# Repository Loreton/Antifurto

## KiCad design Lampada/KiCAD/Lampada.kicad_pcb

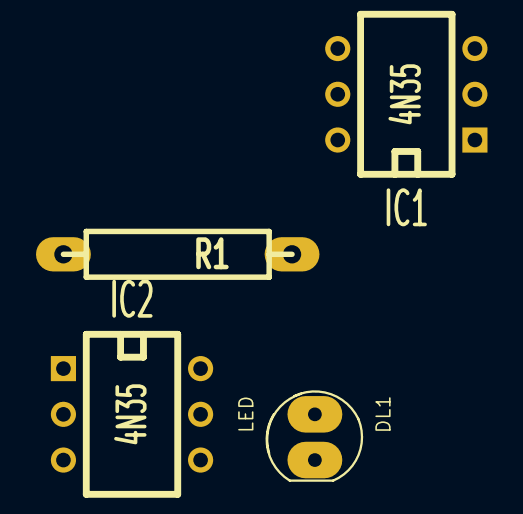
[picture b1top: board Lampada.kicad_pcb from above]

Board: 2 copper layers, 4 parts (0 on the bottom side), 2 nets, no tracks yet.

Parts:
DL1: LED; LnLED-5MM
IC1, IC2: 4N35; DIP-6__300
R1: 2K7; LnRes-500

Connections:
unnamed: DL1.2, IC1.1
unnamed: DL1.1, R1.1

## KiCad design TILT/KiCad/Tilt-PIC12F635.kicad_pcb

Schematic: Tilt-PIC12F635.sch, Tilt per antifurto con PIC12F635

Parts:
C1: .01uF
DL1: LED
K1: PWR
K3: JAlarm
OC1: 4N25; DIP6
P1: CONN_06
R1: 470K
R2: 25K
R4: 33
R5: 47K
SW1: TILT
U1: PIC12F635

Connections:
/Out: R4.1, U1.2 (GP5/CLKIN)
/Tilt: C1.1, R1.2, SW1.2
GND: DL1.2 (K), K1.3, OC1.2, P1.3, SW1.1, U1.8 (VSS)
ICSPCLK: P1.5, U1.6 (GP1/IPCSCLK)
ICSPDAT: P1.4, U1.7 (GP0/IPCSDAT)
unnamed: K3.2 (PM), OC1.4
unnamed: DL1.1 (A), OC1.1, R4.2
unnamed: C1.2, U1.5 (GP2/INT)
unnamed: K3.1, R5.1
unnamed: OC1.5, R5.2
VCC: K1.1, P1.2, R1.1, R2.1, U1.1 (VDD)
VPP/MCLR: P1.1, R2.2, U1.4 (GP3/MCLR)

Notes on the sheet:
Sensore Magnetico Wi-Fi
20uA a riposo
Il condensatore C1 e la resistenza R2 servono per ridurre ulteriormente il consumo. Con i valori indicati R=470K e C=10nF si arriva ad un consumo di circa 70uA a riposo.
OCT serve nel caso dovessi mettere l'accoppiatore ottico lontano dal uP.

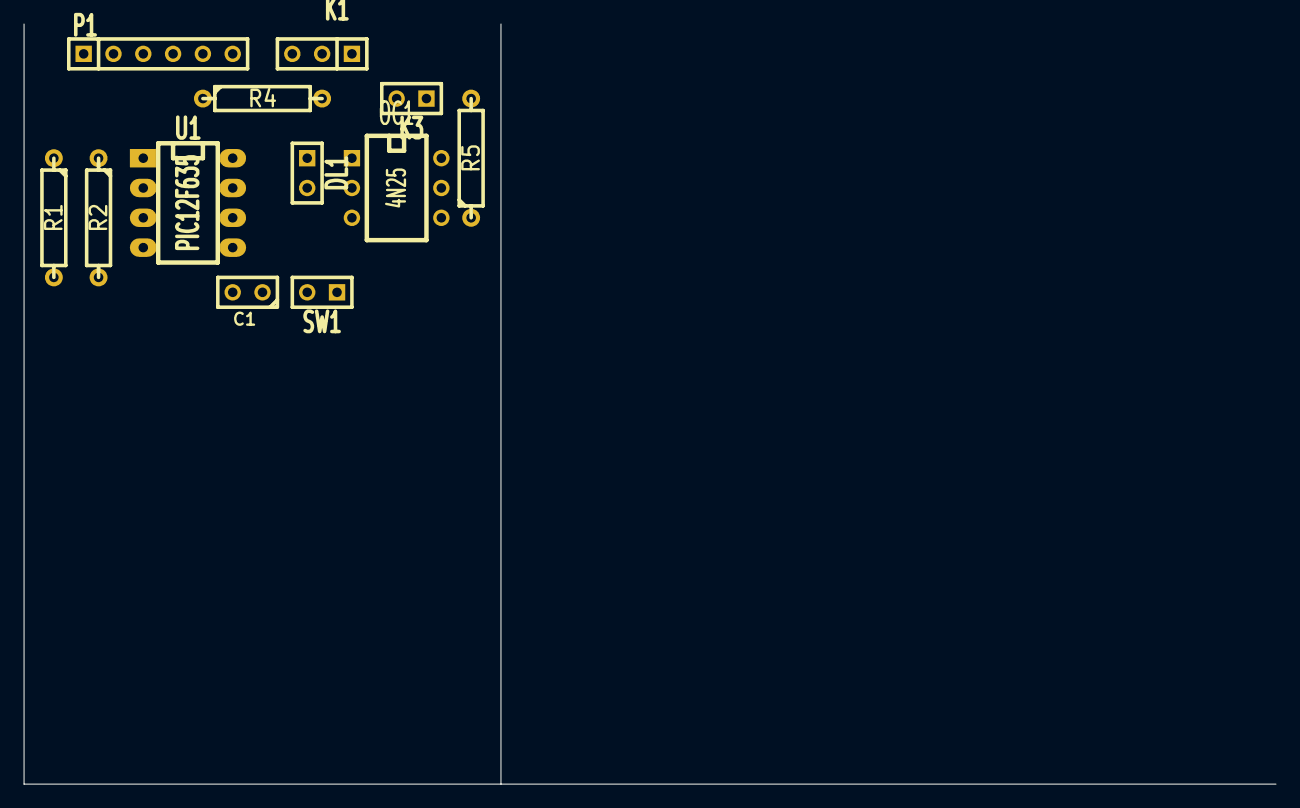
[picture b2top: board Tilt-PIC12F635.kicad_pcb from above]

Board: 4 copper layers, 106.7 x 64.8 mm, 12 parts (0 on the bottom side), 12 nets.

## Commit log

2015-02-10 aggiornato schema Sirena eliminando tutti i circuiti aggiuntivi
2015-02-16 2015-02-16 07:38 - commit with no comment
